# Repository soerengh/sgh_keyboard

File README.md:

First attempt at a custom split KB.

# WIP

## Goals

- Elite C Microcontroller
- split KB with master/slave via TRRS cable
- OLED panel

## Requirements, Layout, etc

- sensibly staggered
- dedicated arrows
- dedicated backspace/del
- max. 3 layers
- 65 or 66 Keys (double space)
- no need for LEDs
- 1 rotary encoder per-side

## Estimated BoM

- 2 Elite C / Pro Micro
- (currently) 68 MX style switches
- 68 1N4148 Diodes
- 2 EC11 Rotary Encoders
- 2 TRRS connectors
- TRRS cable with 2 male sides
- 2 SSD1306 OLED Displays
- 68 Kailh Hotswap Sockets

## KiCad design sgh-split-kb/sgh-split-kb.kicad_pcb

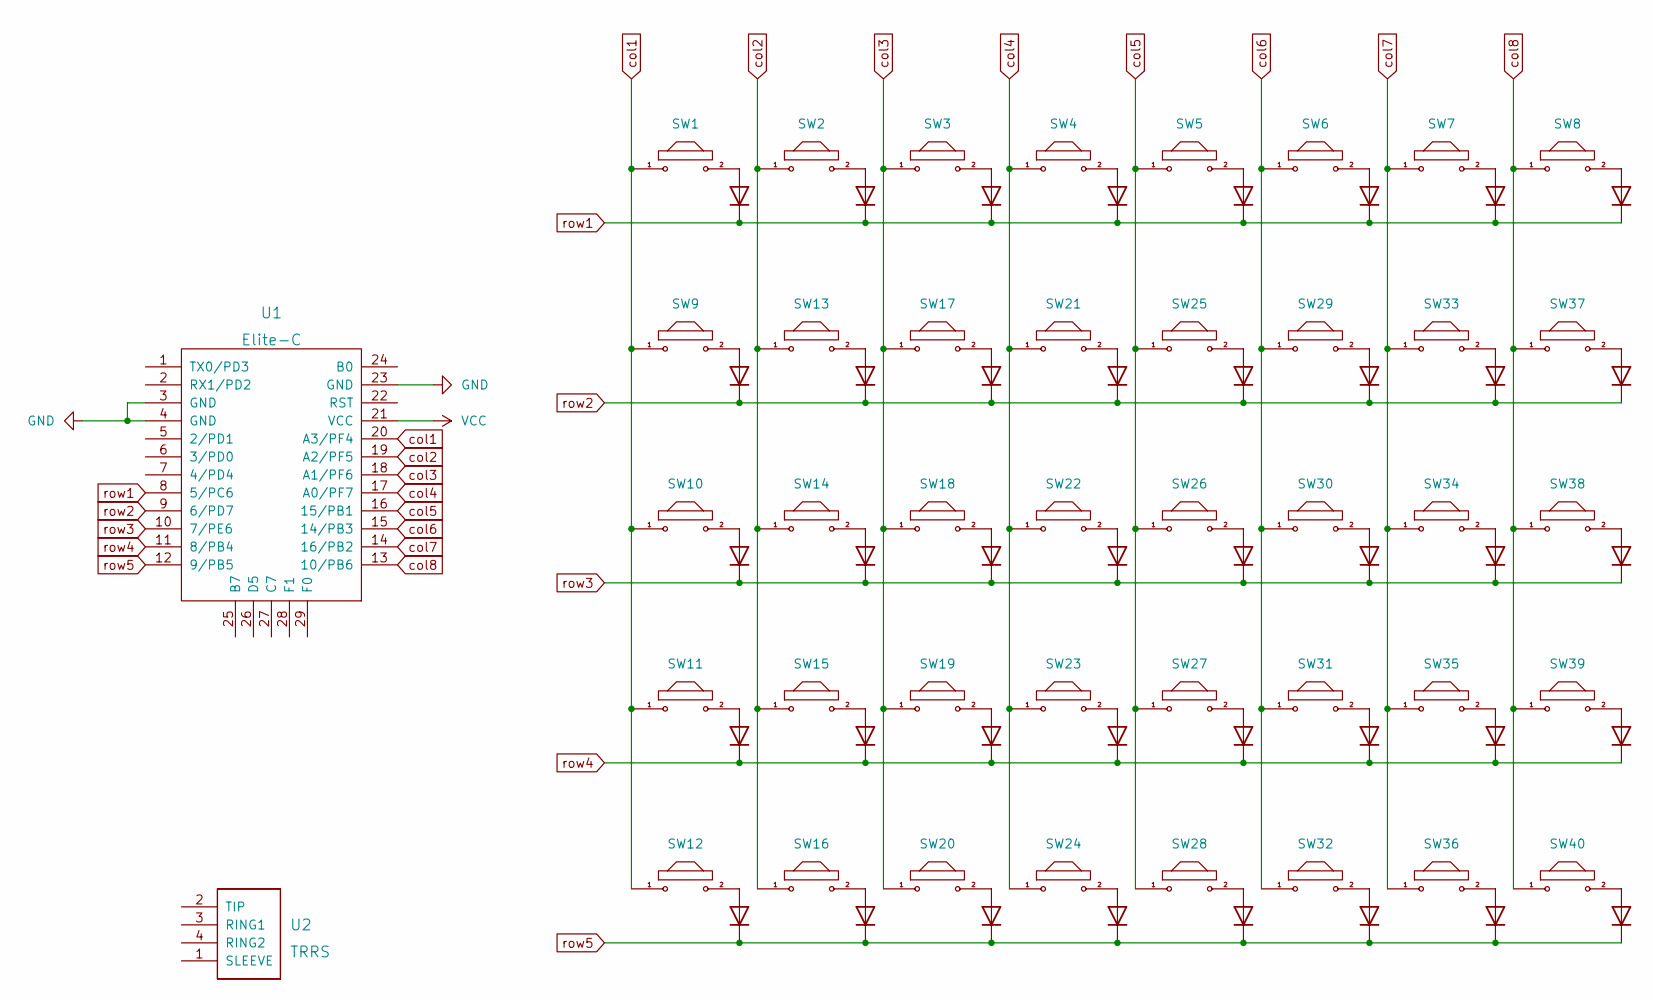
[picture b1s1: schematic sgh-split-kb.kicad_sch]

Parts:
D1, D2, D3, D4, D5, D6, D7, D8, D9, D10, D11, D12, D13, D14, D15, D16, D17, D18, D19, D20, D21, D22, D23, D24, D25, D26, D27, D28, D29, D30, D31, D32, D33, D34, D35, D36, D37, D38, D39, D40: 1N4148; Diode
SW1, SW2, SW3, SW4, SW5, SW6, SW7, SW8, SW9, SW10, SW11, SW12, SW13, SW14, SW15, SW16, SW17, SW18, SW19, SW20, SW21, SW22, SW23, SW24, SW25, SW26, SW27, SW28, SW29, SW30, SW31, SW32, SW33, SW34, SW35, SW36, SW37, SW38, SW39, SW40: MX; MX-Alps-Choc-1U
U1: Elite-C
U2: TRRS; TRRS-PJ-320A

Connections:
GND: U1.3 (GND), U1.4 (GND), U1.23 (GND)
unnamed: D1.2 (A), SW1.2
unnamed: D2.2 (A), SW9.2
unnamed: D3.2 (A), SW10.2
unnamed: D4.2 (A), SW11.2
unnamed: D5.2 (A), SW12.2
unnamed: D6.2 (A), SW2.2
unnamed: D7.2 (A), SW13.2
unnamed: D8.2 (A), SW14.2
unnamed: D9.2 (A), SW15.2
unnamed: D10.2 (A), SW16.2
unnamed: D11.2 (A), SW3.2
unnamed: D12.2 (A), SW17.2
unnamed: D13.2 (A), SW18.2
unnamed: D14.2 (A), SW19.2
unnamed: D15.2 (A), SW20.2
unnamed: D16.2 (A), SW4.2
unnamed: D17.2 (A), SW21.2
unnamed: D18.2 (A), SW22.2
unnamed: D19.2 (A), SW23.2
unnamed: D20.2 (A), SW24.2
unnamed: D21.2 (A), SW5.2
unnamed: D22.2 (A), SW25.2
unnamed: D23.2 (A), SW26.2
unnamed: D24.2 (A), SW27.2
unnamed: D25.2 (A), SW28.2
unnamed: D26.2 (A), SW6.2
unnamed: D27.2 (A), SW29.2
unnamed: D28.2 (A), SW30.2
unnamed: D29.2 (A), SW31.2
unnamed: D30.2 (A), SW32.2
unnamed: D31.2 (A), SW7.2
unnamed: D32.2 (A), SW33.2
unnamed: D33.2 (A), SW34.2
unnamed: D34.2 (A), SW35.2
unnamed: D35.2 (A), SW36.2
unnamed: D36.2 (A), SW8.2
unnamed: D37.2 (A), SW37.2
unnamed: D38.2 (A), SW38.2
unnamed: D39.2 (A), SW39.2
unnamed: D40.2 (A), SW40.2
VCC: U1.21 (VCC)
col1: SW1.1, SW9.1, SW10.1, SW11.1, SW12.1, U1.20 (A3/PF4)
col2: SW2.1, SW13.1, SW14.1, SW15.1, SW16.1, U1.19 (A2/PF5)
col3: SW3.1, SW17.1, SW18.1, SW19.1, SW20.1, U1.18 (A1/PF6)
col4: SW4.1, SW21.1, SW22.1, SW23.1, SW24.1, U1.17 (A0/PF7)
col5: SW5.1, SW25.1, SW26.1, SW27.1, SW28.1, U1.16 (15/PB1)
col6: SW6.1, SW29.1, SW30.1, SW31.1, SW32.1, U1.15 (14/PB3)
col7: SW7.1, SW33.1, SW34.1, SW35.1, SW36.1, U1.14 (16/PB2)
col8: SW8.1, SW37.1, SW38.1, SW39.1, SW40.1, U1.13 (10/PB6)
row1: D1.1 (K), D6.1 (K), D11.1 (K), D16.1 (K), D21.1 (K), D26.1 (K), D31.1 (K), D36.1 (K), U1.8 (5/PC6)
row2: D2.1 (K), D7.1 (K), D12.1 (K), D17.1 (K), D22.1 (K), D27.1 (K), D32.1 (K), D37.1 (K), U1.9 (6/PD7)
row3: D3.1 (K), D8.1 (K), D13.1 (K), D18.1 (K), D23.1 (K), D28.1 (K), D33.1 (K), D38.1 (K), U1.10 (7/PE6)
row4: D4.1 (K), D9.1 (K), D14.1 (K), D19.1 (K), D24.1 (K), D29.1 (K), D34.1 (K), D39.1 (K), U1.11 (8/PB4)
row5: D5.1 (K), D10.1 (K), D15.1 (K), D20.1 (K), D25.1 (K), D30.1 (K), D35.1 (K), D40.1 (K), U1.12 (9/PB5)

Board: 2 copper layers, 82 parts (0 on the bottom side), 54 nets, no tracks yet.

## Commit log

2022-06-12 add readme
2022-06-19 asdf
2022-06-20 basic schematic
2022-06-21 first layout
2022-06-21 add BoM to README
2022-06-21 assign footprints & begin pcb design
2022-06-25 add keymap to README
